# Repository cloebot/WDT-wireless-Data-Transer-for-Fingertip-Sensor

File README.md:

# Improving Robotics Technology via Wireless Data Transfer

This project developed “pre-touch” sensors for robotic fingertips, a significant component in robotic engineering. My goal for devices entails generating power for the sensors, transferring data wirelessly, and controlling up to five sensors at the same time. By measuring the distance between the sensor and an object, algorithms can be used to detect information before ever touching the object.

By applying this innovative technology, sensor robots can be used to help those who rely on the assistance of others for completing everyday tasks. These sensors can lend a hand for those in need by opening a door, picking up fallen objects, pulling wheelchairs, and so on. Up until recently, sensors could only send their data through wires, limiting the overall movement of the robot. The goal of this study is to redevelop the current system of pre-touch sensors to transfer data wirelessly, ultimately controlling up to five sensors at once. As a result, these versatile sensors could someday be applied to any robot in the world.

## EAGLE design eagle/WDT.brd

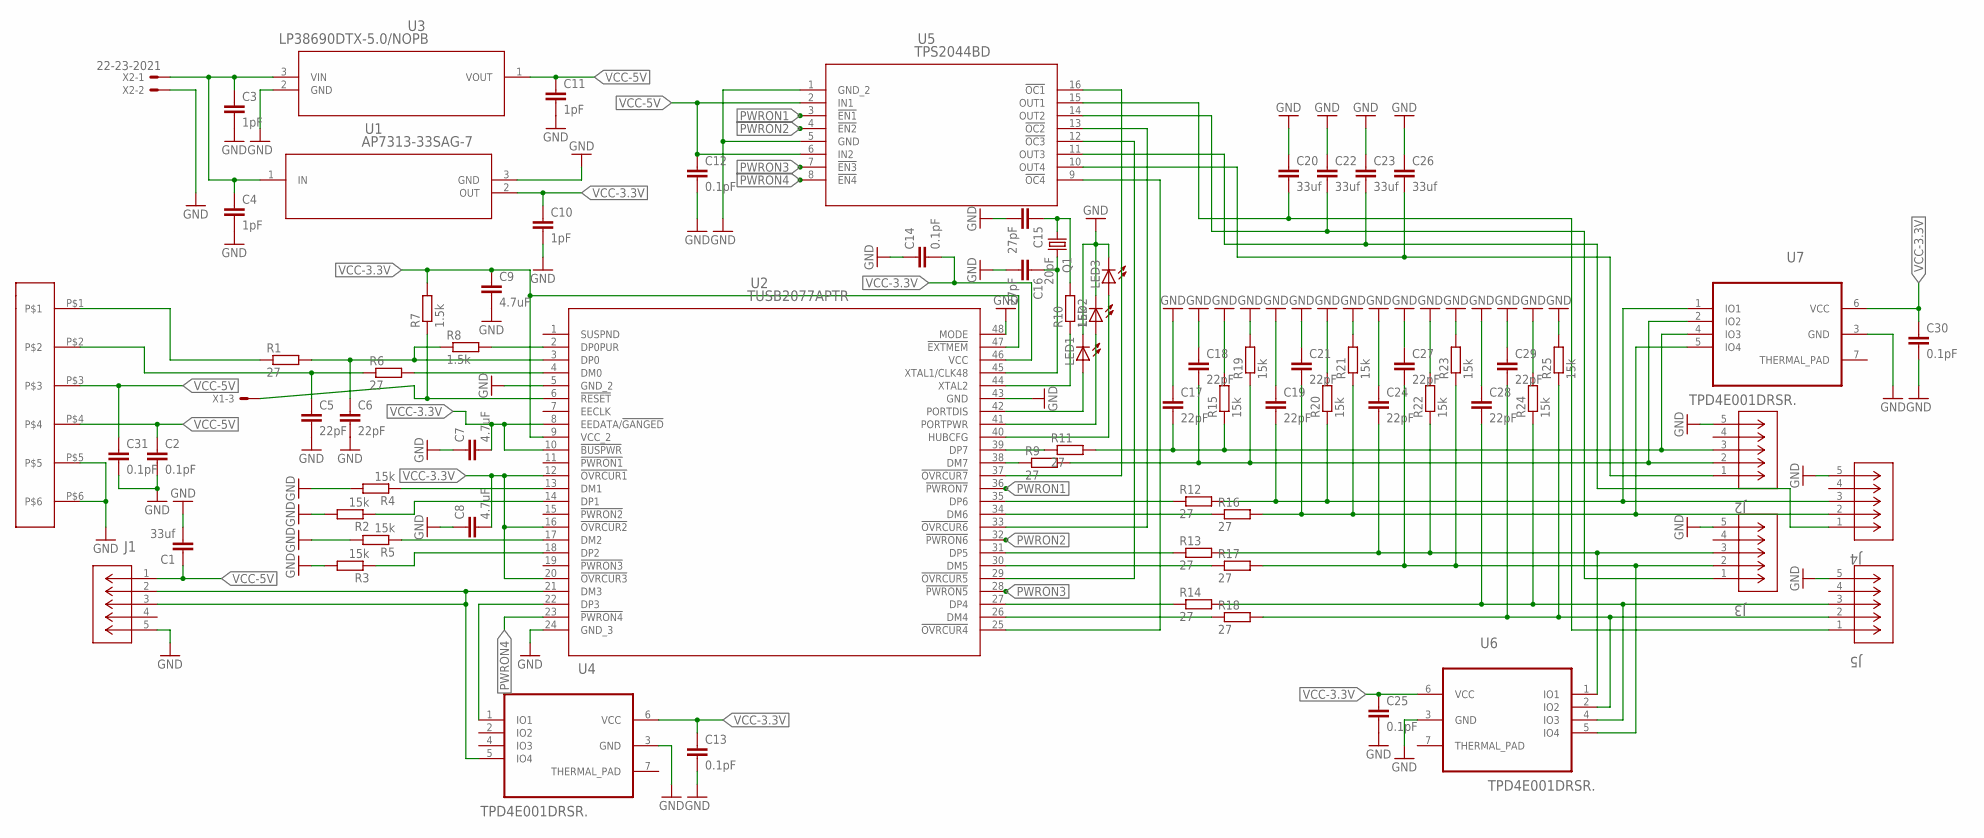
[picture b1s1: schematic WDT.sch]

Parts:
C1, C20, C22, C23, C26: 33uf; C0805
C2, C12, C13, C14, C25, C30, C31: 0.1pF; C0805
C3, C4, C10, C11: 1pF; C0805
C5, C6, C17, C18, C19, C21, C24, C27, C28, C29: 22pF; C0805
C7, C8, C9: 4.7uF; C0805
C15, C16: 27pF; C0805
J1, J2, J3, J4, J5: 1981568-1; CONN_1981568-1
LED1, LED2, LED3: LED_E; LED_1206
Q1: 20pF; CTS406
R1, R6, R9, R11, R12, R13, R14, R16, R17, R18: 27; R0805
R2, R3, R4, R5, R10, R15, R19, R20, R21, R22, R23, R24, R25: 15k; R0805
R7, R8: 1.5k; R0805
U1: AP7313-33SAG-7; SOT-23
U2: TUSB2077APTR; PT48
U3: LP38690DTX-5.0/NOPB; TD03B
U4, U6, U7: TPD4E001DRSR.; SON95P315X315X80-7N
U5: TPS2044BD; D16
U$1: HEADER-6PIN-50MIL; PIN-4-1.27MMPITCH
X1: 22-23-2051
X2: 22-23-2021

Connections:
GND: C1.2, C2.2, C3.2, C4.2, C5.2, C6.2, C7.1, C8.1, C9.2, C10.2, C11.2, C12.2, C13.2, C14.1, C15.2, C16.2, C17.1, C18.1, C19.1, C20.1, C21.1, C22.1, C23.1, C24.1, C25.2, C26.1, C27.1, C28.1, C29.1, C30.2, C31.2, J1.5, J2.5, J3.5, J4.5, J5.5, LED1.C, LED2.C, LED3.C, R2.2, R3.2, R4.2, R5.2, R15.2, R19.2, R20.2, R21.2, R22.2, R23.2, R24.2, R25.2, U1.3 (GND), U2.5 (GND_2), U2.24 (GND_3), U2.43 (GND), U2.48 (MODE), U3.2 (GND), U4.3 (GND), U5.1 (GND_2), U5.5 (GND), U6.3 (GND), U7.3 (GND), U$1.P$5, U$1.P$6, X2.2; also elsewhere on the board
N27: U2.37 (!OVRCUR7), U5.16 (!OC1)
unnamed 2: C3.1, C4.1, U1.1 (IN), U3.3 (VIN), X2.1; also elsewhere on the board
unnamed 3: R7.1, U2.6 (!RESET), X1.3; also elsewhere on the board
unnamed: R8.2, U2.2 (DP0PUR)
unnamed: R10.1, U2.44 (XTAL2)
unnamed: R5.1, U2.17 (DM2)
unnamed: C24.2, J3.3, R13.2, R22.1, U6.1 (IO1)
unnamed: C27.2, J3.2, R17.2, R23.1, U6.5 (IO4)
unnamed: C22.2, J3.1, U5.14 (OUT2)
unnamed: LED1.A, U2.42 (PORTDIS)
unnamed: C17.2, J2.3, R11.2, R15.1, U7.4 (IO3)
unnamed: C18.2, J2.2, R9.2, R19.1, U7.2 (IO2)
unnamed: C19.2, J4.3, R12.2, R20.1, U7.1 (IO1)
unnamed: C21.2, J4.2, R16.2, R21.1, U7.5 (IO4)
unnamed: C28.2, J5.3, R14.2, R24.1, U6.4 (IO3)
unnamed: C29.2, J5.2, R18.2, R25.1, U6.2 (IO2)
unnamed: R14.1, U2.27 (DP4)
unnamed: R9.1, U2.38 (DM7)
unnamed: R11.1, U2.39 (DP7)
unnamed: C6.1, R1.2, R8.1, U2.3 (DP0)
unnamed 21: C5.1, R6.1, U$1.P$2; also elsewhere on the board
unnamed: C26.2, J2.1, U5.10 (OUT4)
unnamed: C23.2, J4.1, U5.11 (OUT3)
unnamed: C20.2, J5.1, U5.15 (OUT1)
unnamed: R4.1, U2.13 (DM1)
unnamed: R3.1, U2.18 (DP2)
unnamed: U2.29 (!OVRCUR5), U5.12 (!OC3)
unnamed 28: R1.1, U$1.P$1; also elsewhere on the board
unnamed: U2.33 (!OVRCUR6), U5.13 (!OC2)
unnamed: R6.2, U2.4 (DM0)
unnamed: R2.1, U2.14 (DP1)
unnamed: R12.1, U2.35 (DP6)
unnamed: R17.1, U2.30 (DM5)
unnamed: U2.25 (!OVRCUR4), U5.9 (!OC4)
unnamed: R13.1, U2.31 (DP5)
unnamed: R18.1, U2.26 (DM4)
unnamed: R16.1, U2.34 (DM6)
unnamed: LED2.A, U2.41 (PORTPWR)
unnamed: LED3.A, U2.40 (HUBCFG)
unnamed: C16.1, Q1.3 (2), U2.45 (XTAL1/CLK48)
unnamed: C15.1, Q1.1, R10.2
PWRON1: U2.36 (!PWRON7), U5.3 (!EN1)
PWRON2: U2.32 (!PWRON6), U5.4 (!EN2)
PWRON3: U2.28 (!PWRON5), U5.7 (!EN3)
PWRON4: U2.23 (!PWRON4), U5.8 (!EN4)
VCC-3.3V: C7.2, C8.2, C9.1, C10.1, C13.1, C14.2, C25.1, C30.1, R7.2, U1.2 (OUT), U2.8 (EEDATA/!GANGED), U2.9 (VCC_2), U2.10 (!BUSPWR), U2.12 (!OVRCUR1), U2.16 (!OVRCUR2), U2.20 (!OVRCUR3), U2.46 (VCC), U2.47 (!EXTMEM), U4.6 (VCC), U6.6 (VCC), U7.6 (VCC)
VCC-5V: C1.1, C2.1, C11.1, C12.1, C31.1, J1.1, U3.1 (VOUT), U5.2 (IN1), U5.6 (IN2), U$1.P$3, U$1.P$4; also elsewhere on the board

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
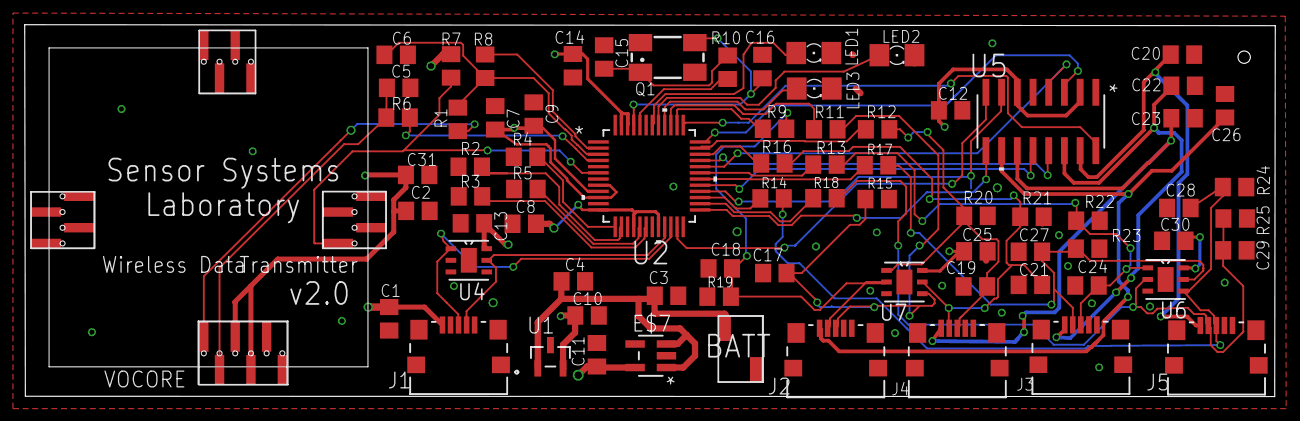
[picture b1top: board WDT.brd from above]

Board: 4 copper layers, 101.2 x 30.1 mm, 77 parts (0 on the bottom side), 50 nets.

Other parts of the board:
E$1: FEMALE-POWER
E$2, E$4, E$5, E$6: 850-10-050-30-001101
E$7: MF05A-M

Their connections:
GND: E$1.P$2, E$4.P$5, E$4.P$6, E$7.2, E$7.4; also elsewhere on the board
unnamed 2: E$1.P$1, E$7.1, E$7.3; also elsewhere on the board
unnamed 3: E$5.P$1; also elsewhere on the board
unnamed 21: E$4.P$2; also elsewhere on the board
unnamed 28: E$4.P$1; also elsewhere on the board
VCC-5V: E$4.P$3, E$4.P$4, E$7.5; also elsewhere on the board
